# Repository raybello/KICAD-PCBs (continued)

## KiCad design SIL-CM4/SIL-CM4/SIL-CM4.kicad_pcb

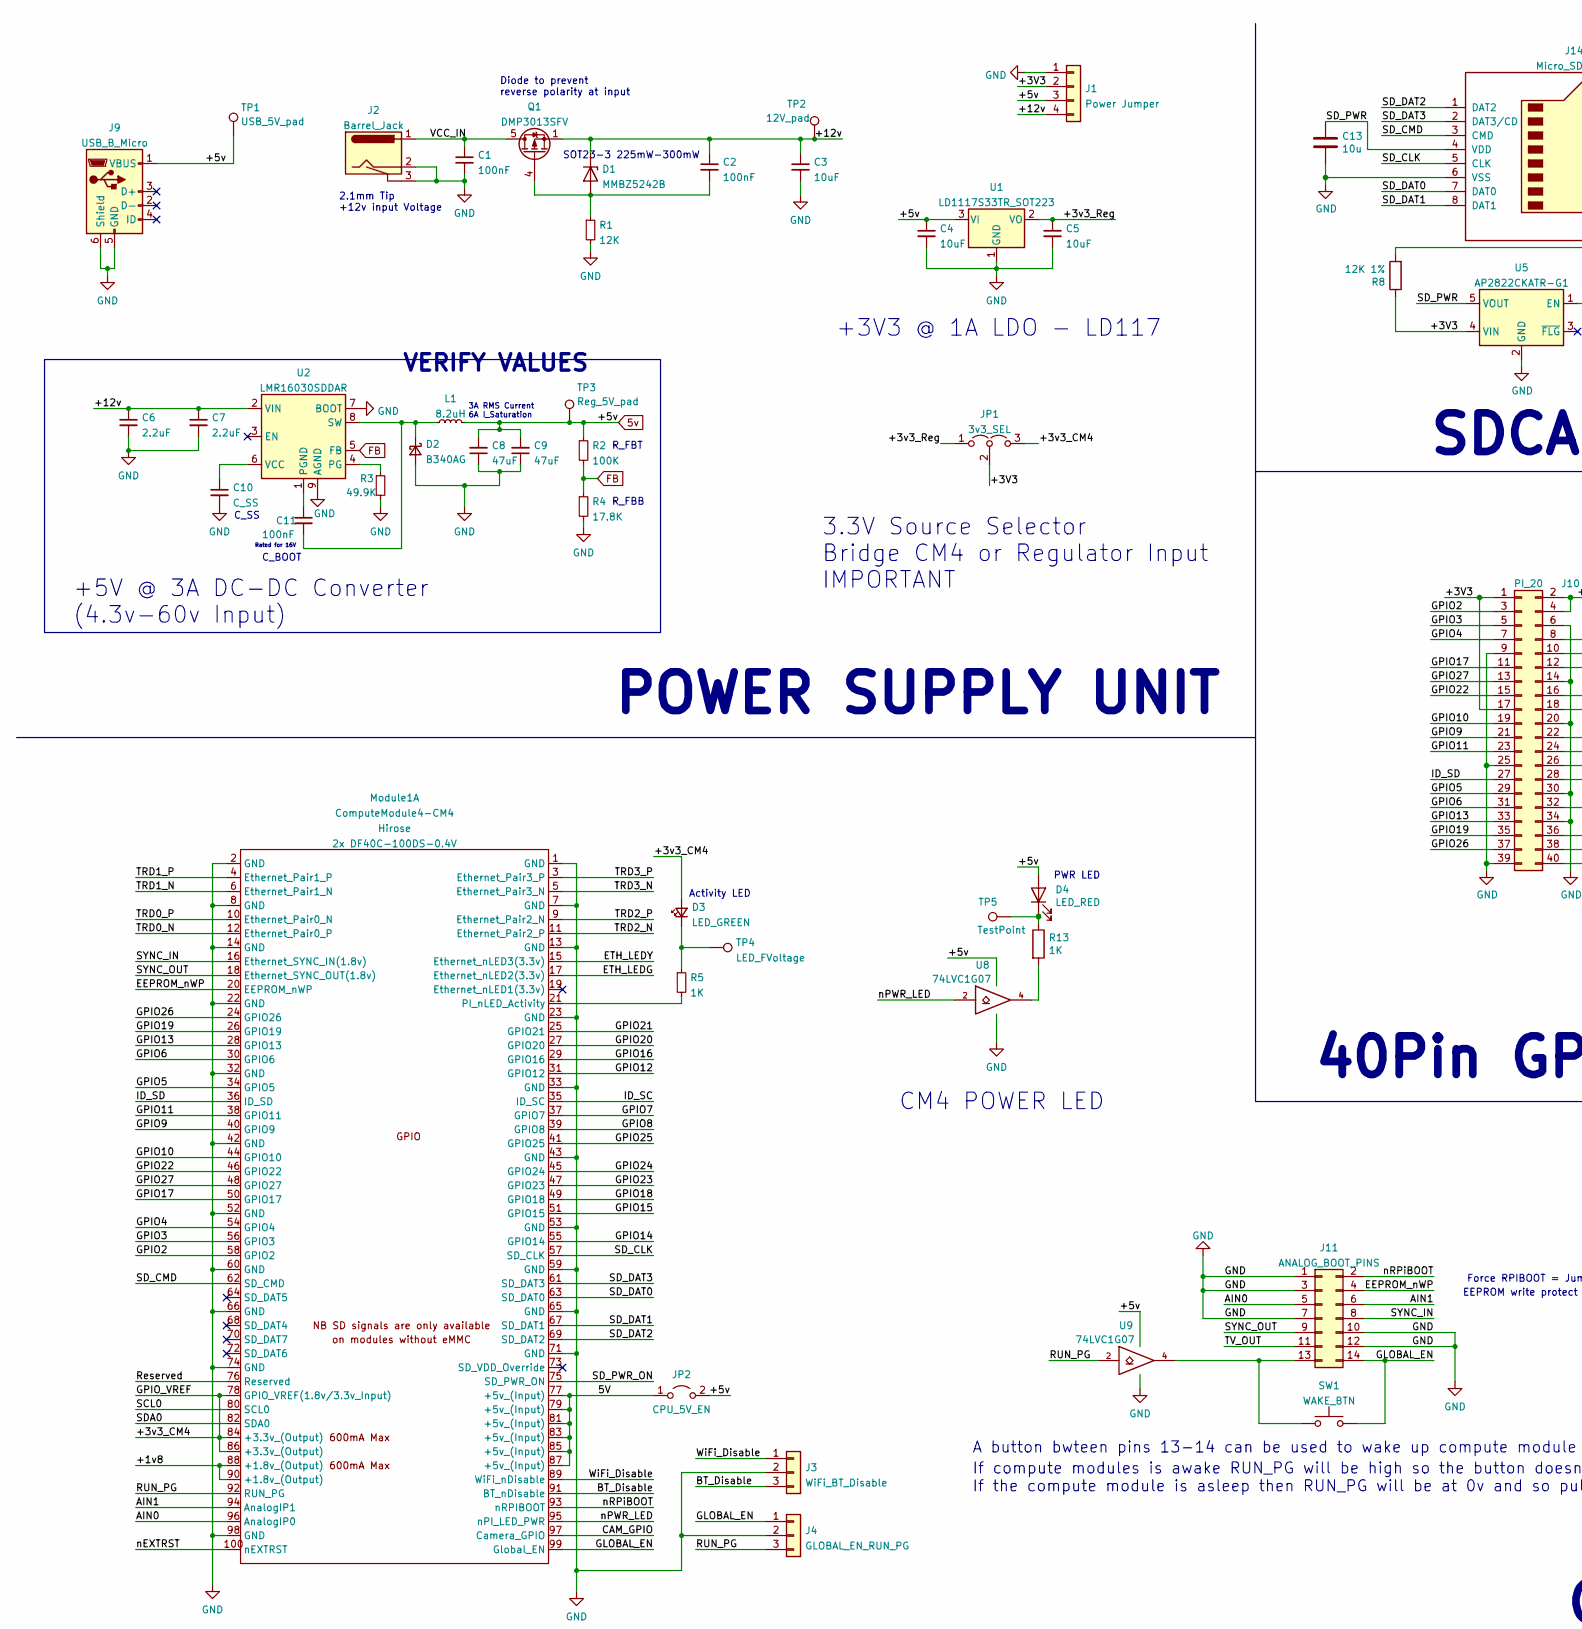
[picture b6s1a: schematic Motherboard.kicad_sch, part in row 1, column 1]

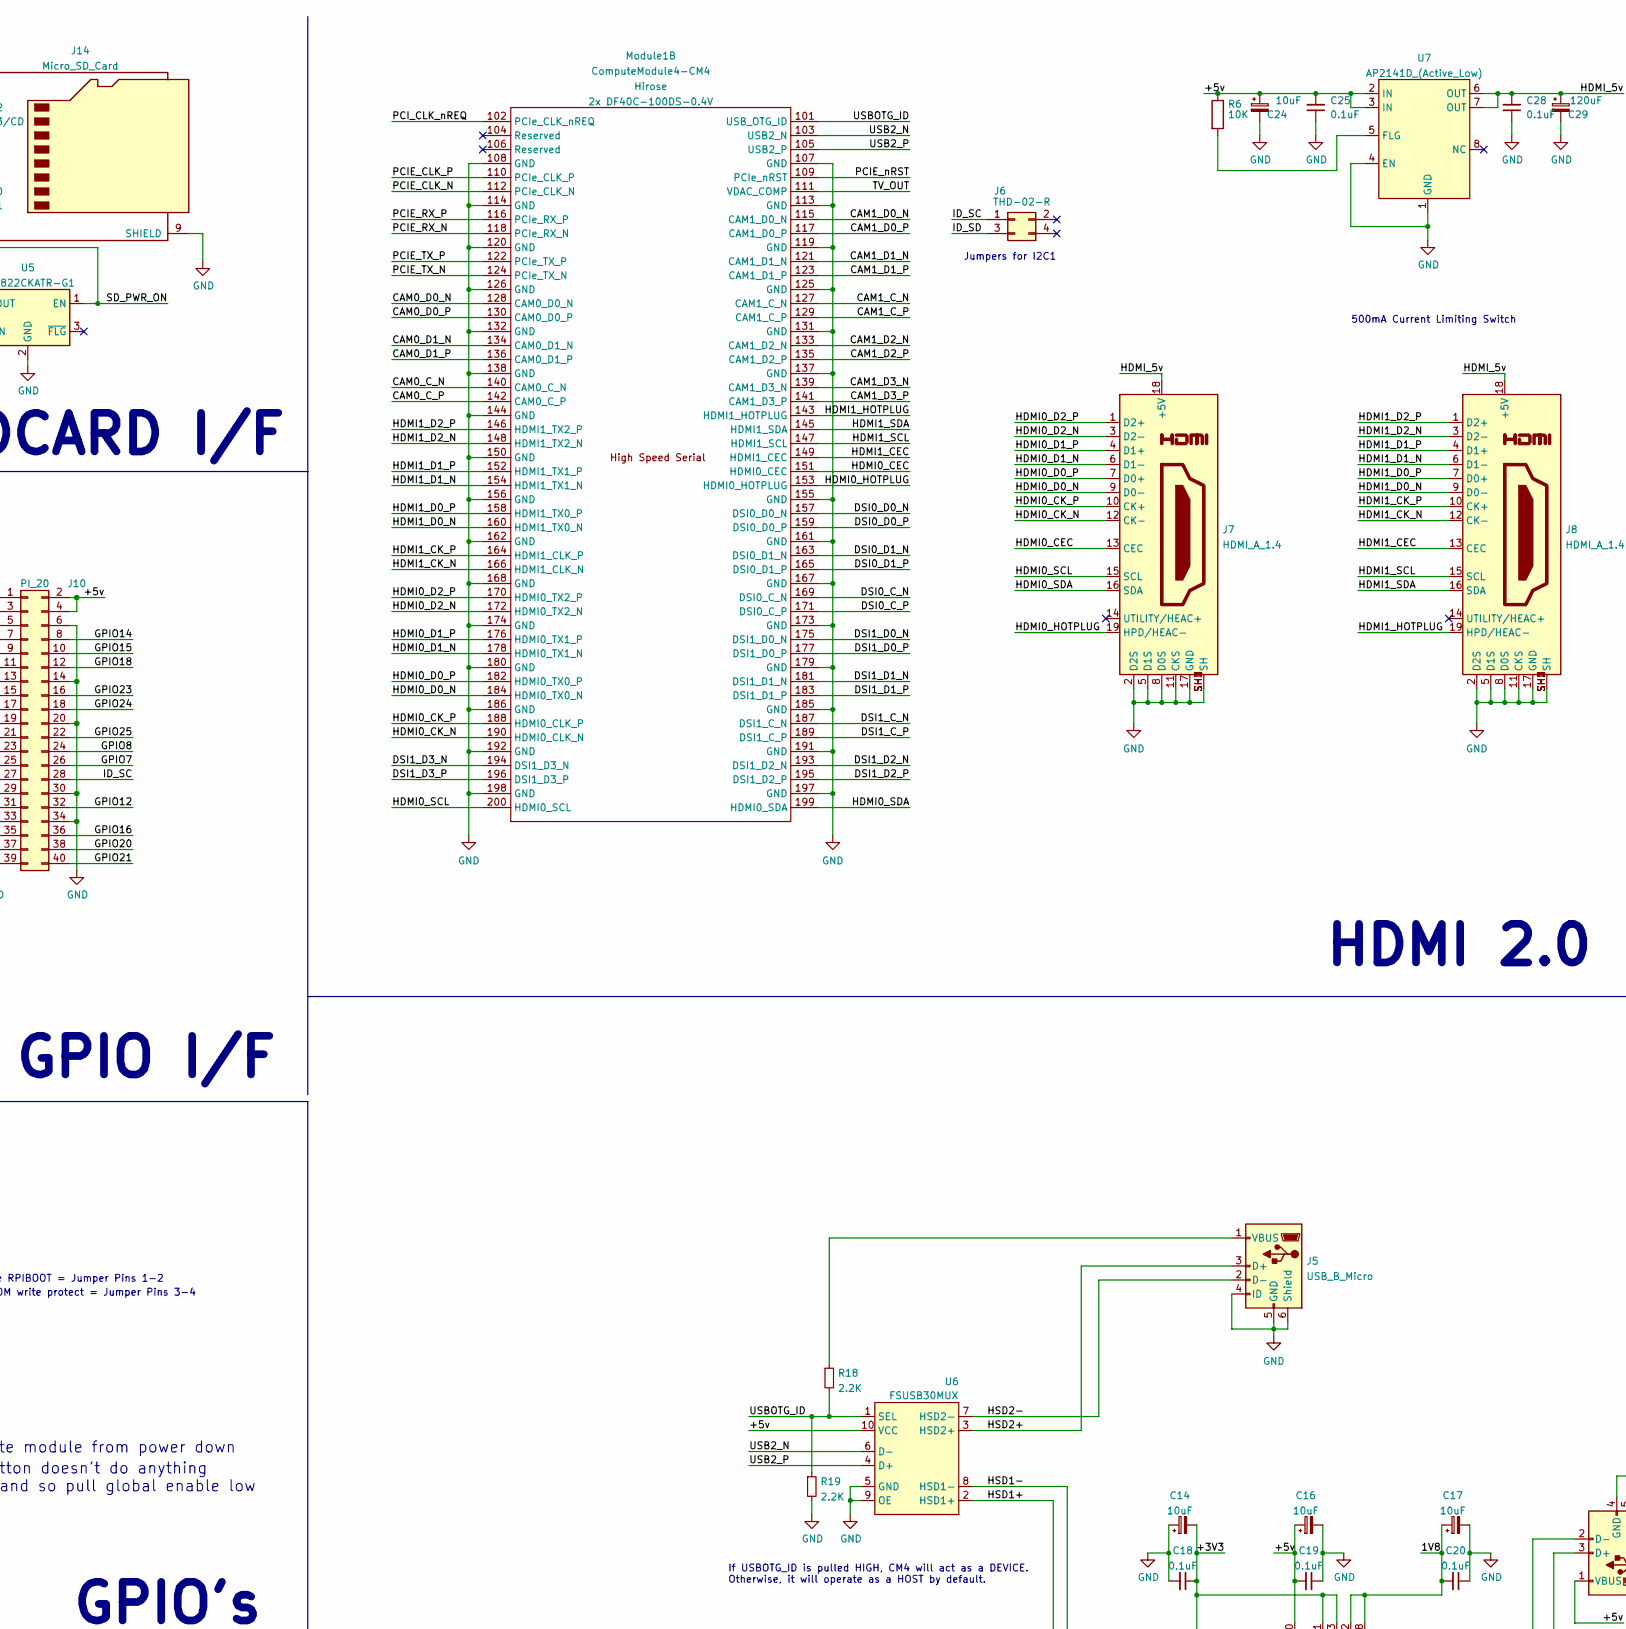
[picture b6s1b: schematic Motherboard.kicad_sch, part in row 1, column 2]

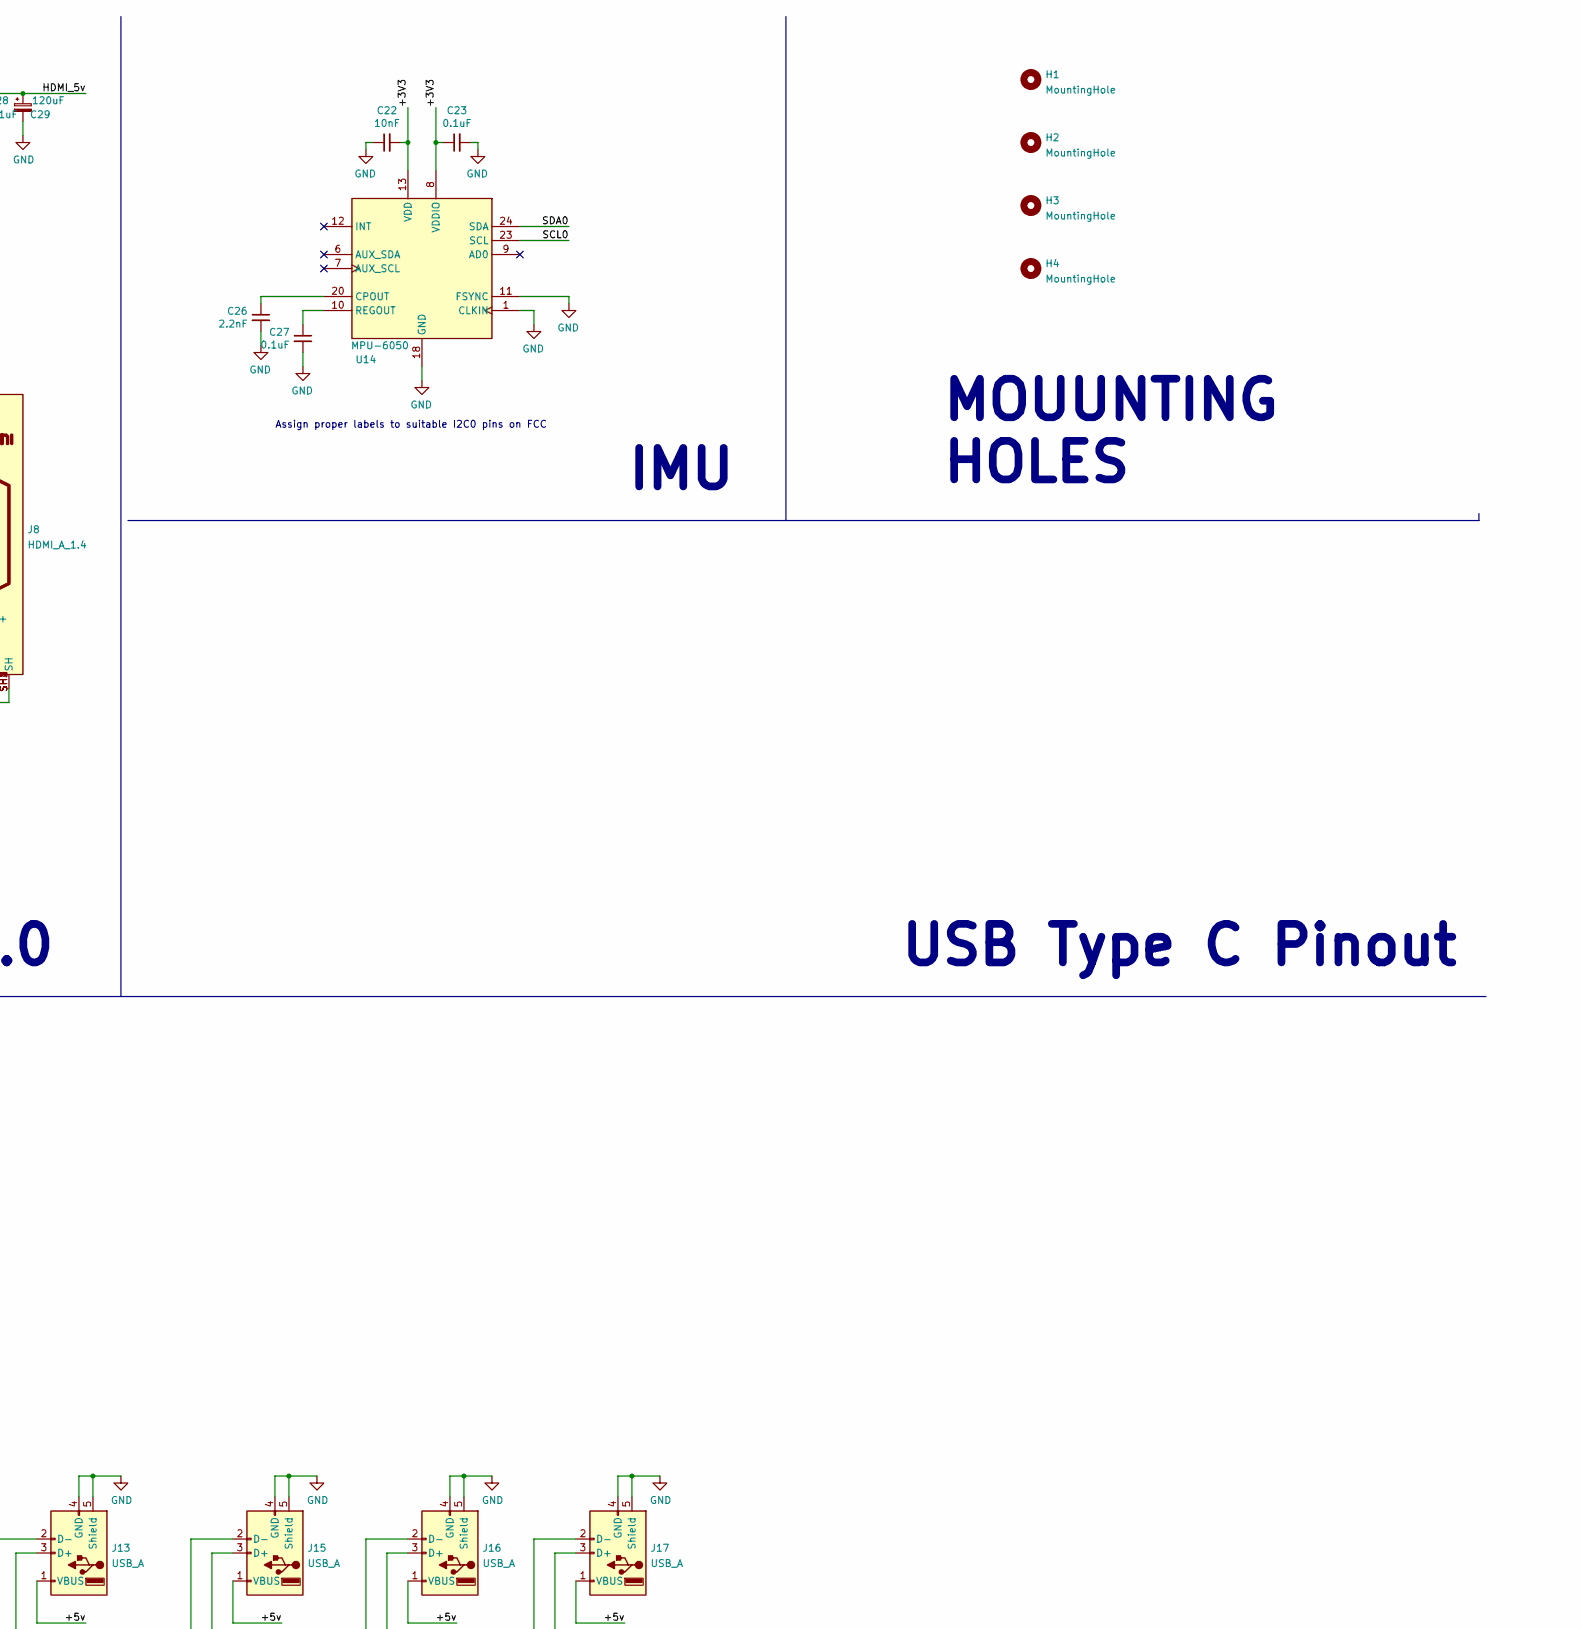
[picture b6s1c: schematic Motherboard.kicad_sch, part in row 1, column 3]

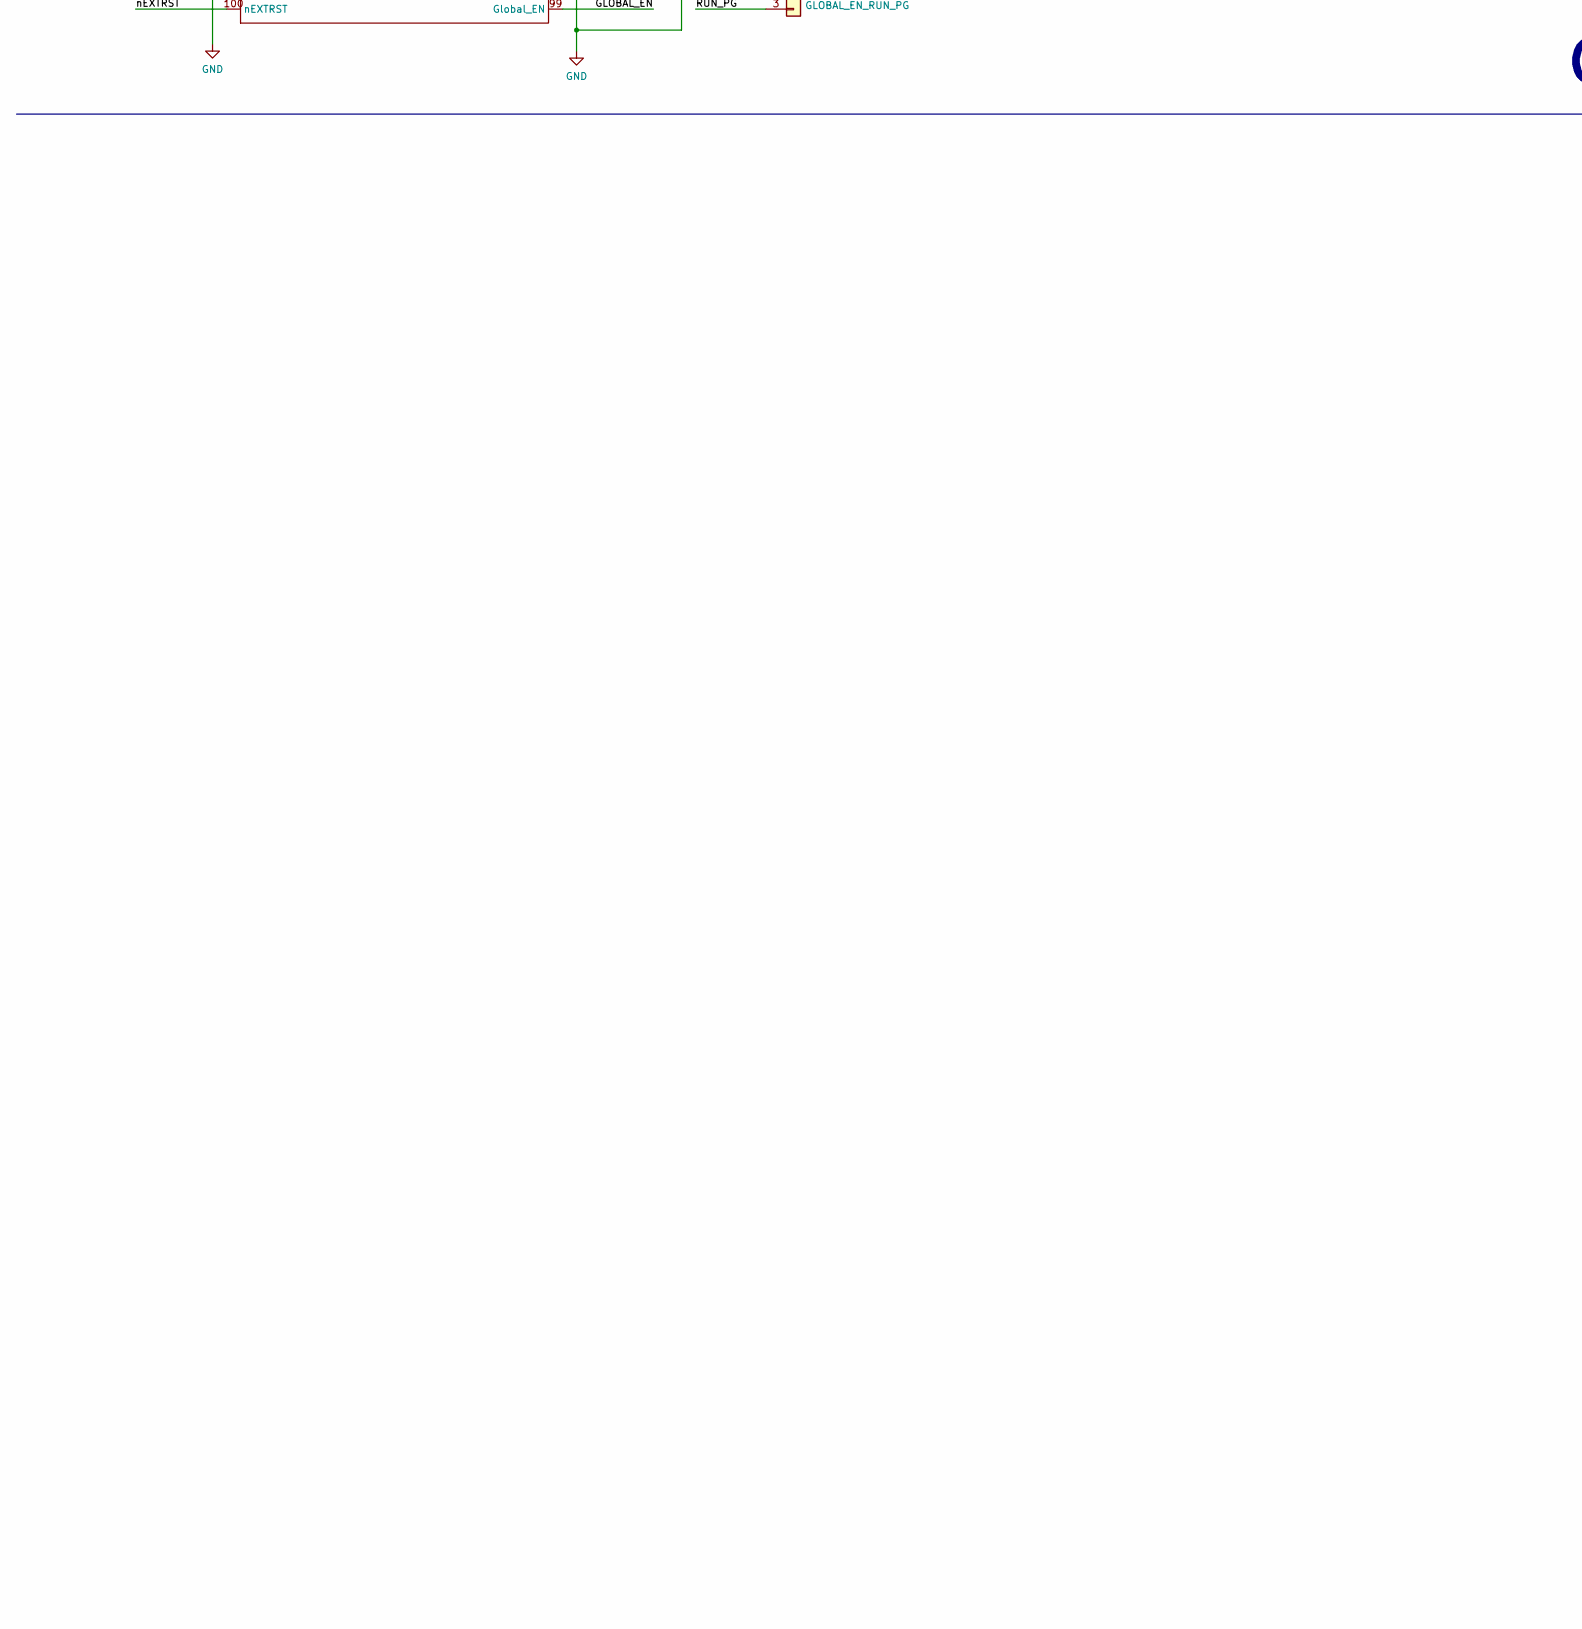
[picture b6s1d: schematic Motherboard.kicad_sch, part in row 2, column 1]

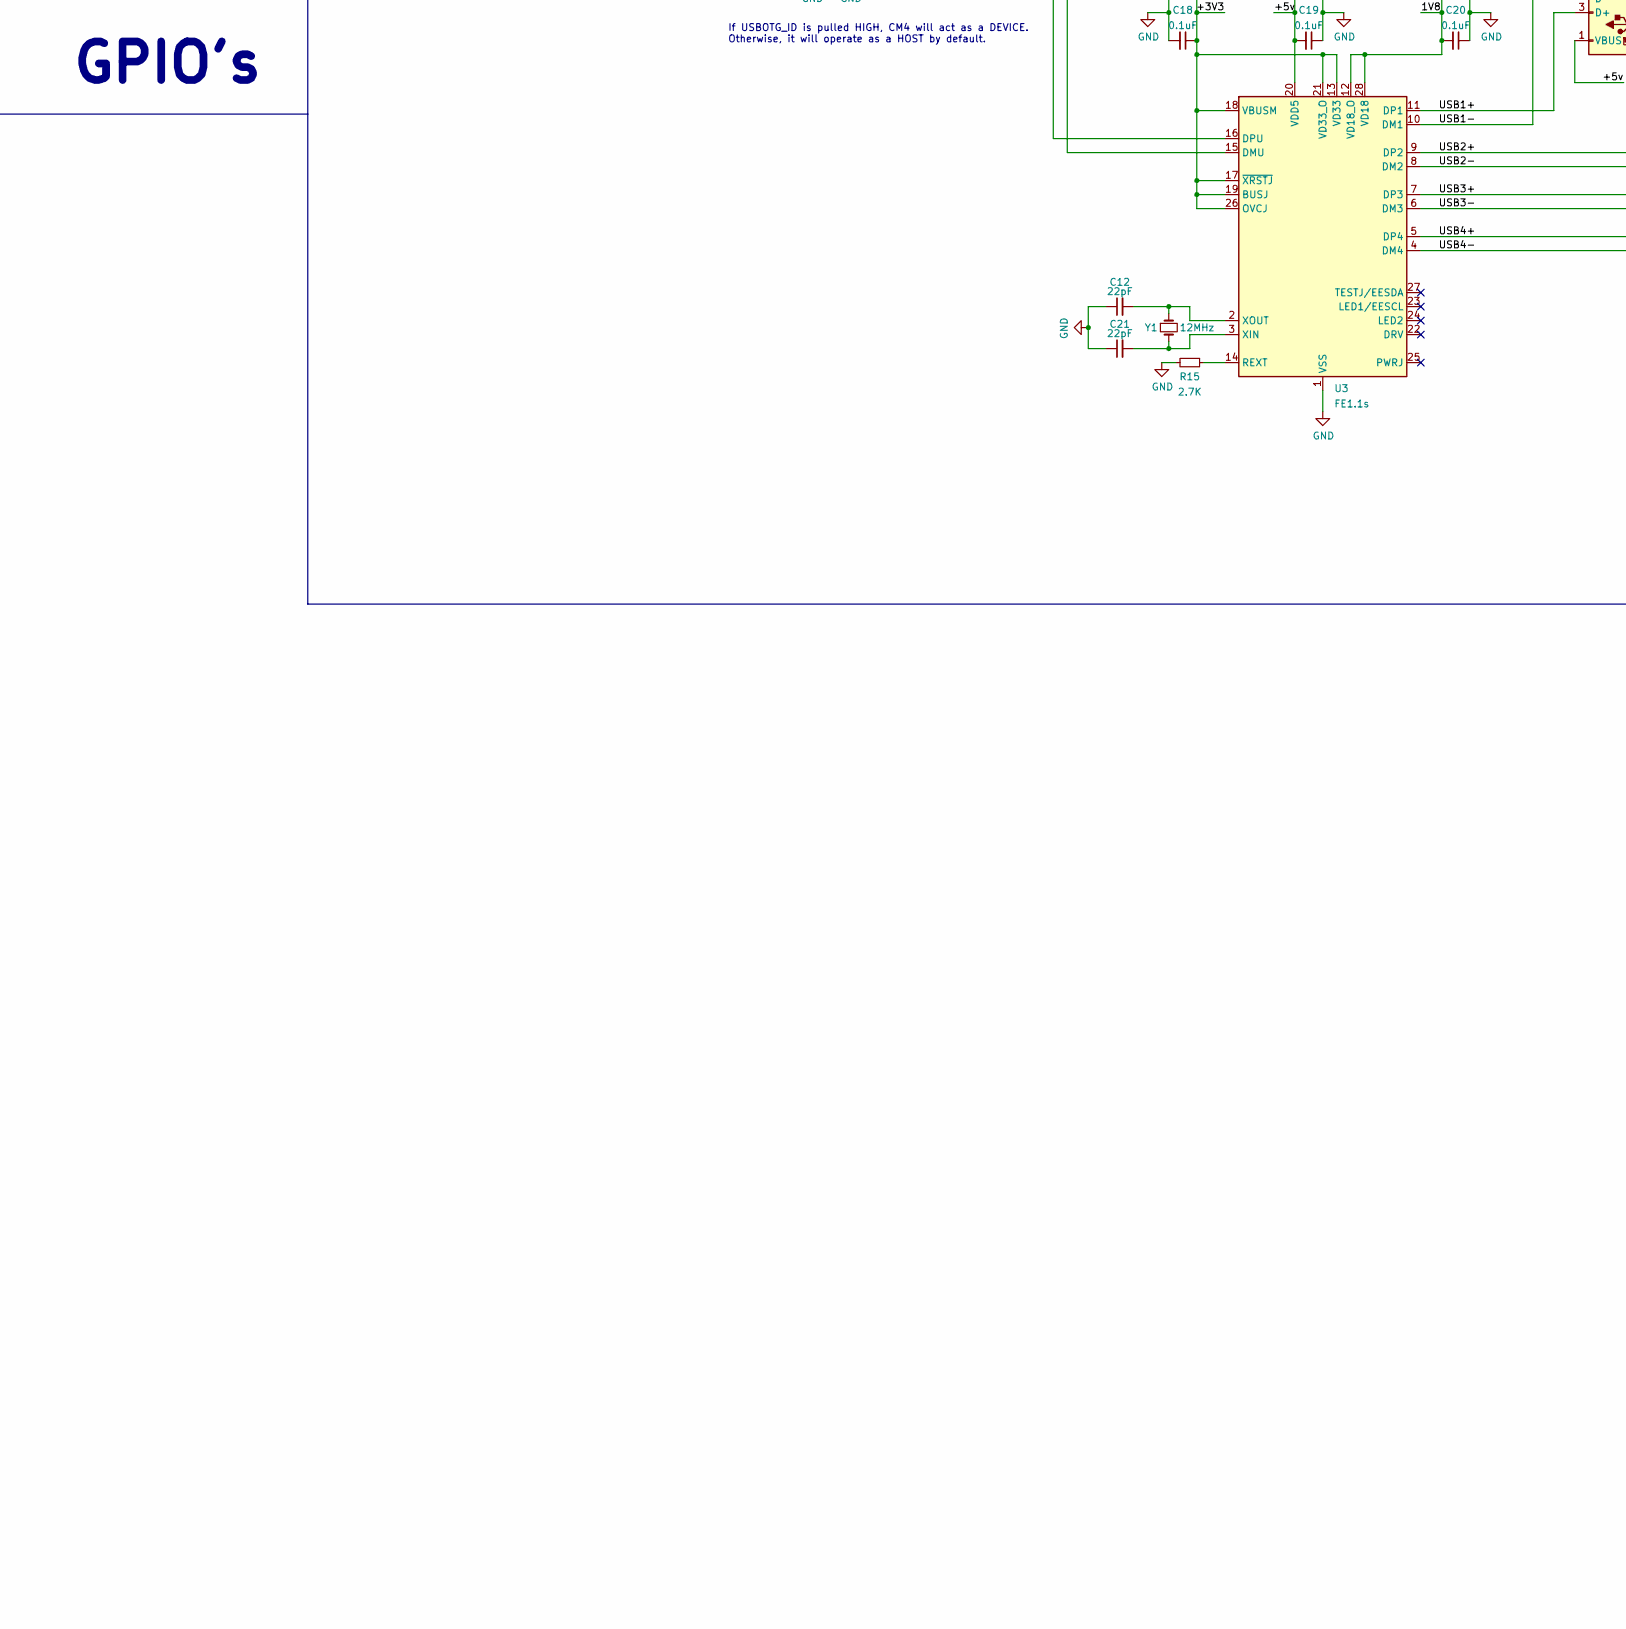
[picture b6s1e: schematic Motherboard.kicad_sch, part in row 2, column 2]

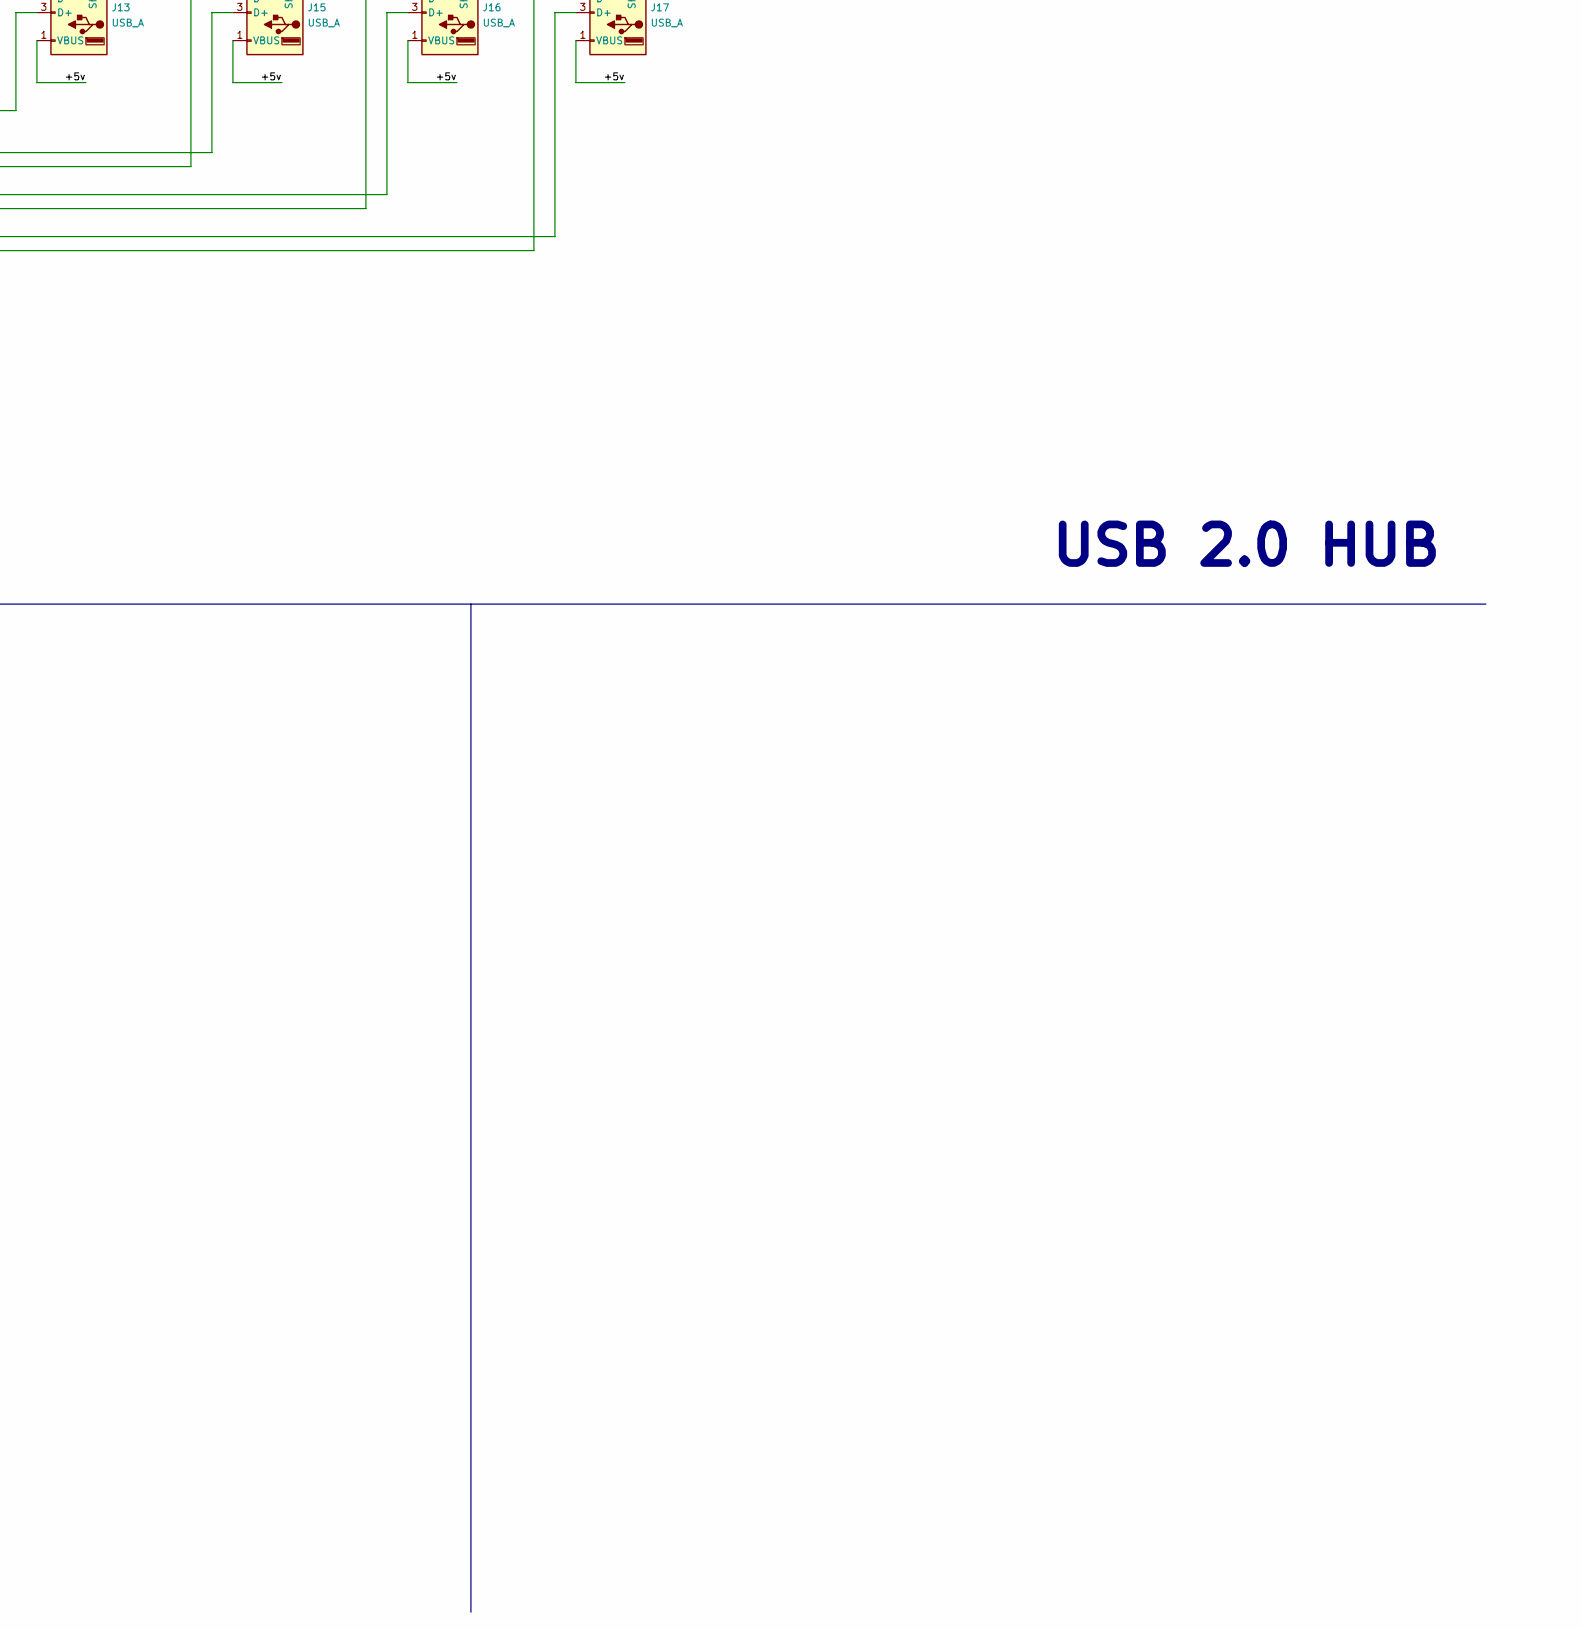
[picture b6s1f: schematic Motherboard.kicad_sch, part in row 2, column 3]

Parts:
C1, C2, C11: 100nF; C_0402_1005Metric
C3, C4, C5, C14, C16, C17, C24: 10uF; C_0402_1005Metric
C6, C7: 2.2uF; C_0402_1005Metric
C8, C9: 47uF; C_0402_1005Metric
C10: C_SS; C_0402_1005Metric
C12, C21: 22pF; C_0402_1005Metric
C13: 10u; C_0402_1005Metric; Part Description 10uF 10% 10V Ceramic Capacitor X7R 0805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
C18, C19, C20, C25, C28: 0.1uF; C_0402_1005Metric
C22: 10nF; C_0402_1005Metric_Pad0.74x0.62mm_HandSolder
C23, C27: 0.1uF; C_0402_1005Metric_Pad0.74x0.62mm_HandSolder
C26: 2.2nF; C_0402_1005Metric_Pad0.74x0.62mm_HandSolder
C29: 120uF; C_0402_1005Metric
D1: MMBZ5242B; D_SOT-23_ANK; LCSC C193729
D2: B340AG; D_SMC; LCSC C433997
D3: LED_GREEN; LED_0402_1005Metric
D4: LED_RED; LED_0402_1005Metric; Part Description Red 620nm LED Indication - Discrete 2.2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
H1, H2, H3, H4: MountingHole; MountingHole_3mm_Pad_Via
J1: Power Jumper; PinHeader_1x04_P2.54mm_Vertical
J2: Barrel_Jack; BarrelJack_CUI_PJ-063AH_Horizontal_CircularHoles; LCSC C381112
J3: WiFi_BT_Disable; PinHeader_1x03_P2.54mm_Vertical
J4: GLOBAL_EN_RUN_PG; PinHeader_1x03_P2.54mm_Vertical
J5, J9: USB_B_Micro; USB_Micro-B_Amphenol_10118194_Horizontal; LCSC C132563
J6: THD-02-R; PinHeader_2x02_P2.54mm_Vertical; Part Description PinHeader_2x02_P2.54mm_Vertical
J7, J8: HDMI_A_1.4; EDAC 690-019-298-412; LCSC C138388
J10: PI_20; PinHeader_2x20_P2.54mm_Vertical; Part Description PinHeader_2x20_P2.54mm_Vertical
J11: ANALOG_BOOT_PINS; PinHeader_2x07_P2.54mm_Vertical
J13, J15, J16, J17: USB_A; USB_A_Molex_67643_Horizontal
J14: Micro_SD_Card; microSD_HC_Wuerth_693072010801
JP1: 3v3_SEL; SolderJumper-3_P1.3mm_Open_RoundedPad1.0x1.5mm
JP2: CPU_5V_EN; SolderJumper-2_P1.3mm_Open_RoundedPad1.0x1.5mm
L1: 8.2uH; L_Bourns_SRP7028A_7.3x6.6mm; LCSC Mouser 652-SRP7028AA-8R2M
Module1: ComputeModule4-CM4; Raspberry-Pi-4-Compute-Module
Q1: DMP3013SFV; Diodes_PowerDI3333-8
R1: 12K; R_0402_1005Metric
R2: 100K; R_0402_1005Metric
R3: 49.9K; R_0402_1005Metric
R4: 17.8K; R_0402_1005Metric
R5: 1K; R_0402_1005Metric
R6: 10K; R_0402_1005Metric; Part Description Resistor 2.2K M1005 1% 63mW
R8: 12K 1%; R_0402_1005Metric; Part Description Resistor 12K M1005 1% 63mW
R13: 1K; R_0402_1005Metric; Part Description Resistor 1K M1005 1% 63mW
R15: 2.7K; R_0402_1005Metric
R18, R19: 2.2K; R_0402_1005Metric
SW1: WAKE_BTN; SW_SPST_PTS810
TP1: USB_5V_pad; TestPoint_Pad_D2.5mm
TP2: 12V_pad; TestPoint_Pad_D2.5mm
TP3: Reg_5V_pad; TestPoint_Pad_D2.5mm
TP4: LED_FVoltage; TestPoint_Pad_D2.5mm
TP5: TestPoint; TestPoint_Pad_D2.5mm
U1: LD1117S33TR_SOT223; SOT-223-3_TabPin2; LCSC C347229
U2: LMR16030SDDAR; Texas_HSOP-8-1EP_3.9x4.9mm_P1.27mm_ThermalVias; LCSC C136648
U3: FE1.1s; SSOP-28_3.9x9.9mm_P0.635mm
U5: AP2822CKATR-G1; SOT-23-5
U6: FSUSB30MUX; SOP50P490X110-10N; LCSC 512-FSUSB30MUX
U7: AP2141D_(Active_Low); MSOP-8-1EP_3x3mm_P0.65mm_EP1.68x1.88mm
U8, U9: 74LVC1G07; SOT-23-5; LCSC Mouser 595-74LVC1G07DBVTE4
U14: MPU-6050; InvenSense_QFN-24_4x4mm_P0.5mm
Y1: 12MHz; Crystal_SMD_TXC_7A-2Pin_5x3.2mm; LCSC C557138

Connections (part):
5v: C4.1, C8.2, C9.2, C16.1, C19.2, C24.1, C25.2, D4.2 (A), J1.3, J9.1 (VBUS), J10.2, J10.4, J13.1 (VBUS), J15.1 (VBUS), J16.1 (VBUS), J17.1 (VBUS), JP2.2 (B), L1.2, R2.1, R6.1, TP1.1, TP3.1, U1.3 (VI), U3.20 (VDD5), U6.10 (VCC), U7.2 (IN), U7.3 (IN), U8.5 (VCC), U9.5 (VCC)
/SIL-Motherboard/1V8: C17.1, C20.2, U3.12 (VD18_O), U3.28 (VD18)
/SIL-Motherboard/5V: JP2.1 (A), Module1.77 (+5v_(Input)), Module1.79 (+5v_(Input)), Module1.81 (+5v_(Input)), Module1.83 (+5v_(Input)), Module1.85 (+5v_(Input)), Module1.87 (+5v_(Input))
/SIL-Motherboard/+1v8: Module1.88 (+1.8v_(Output)), Module1.90 (+1.8v_(Output))
/SIL-Motherboard/+3V3: C14.2, C18.1, C22.2, C23.1, J1.2, J10.1, J10.17, JP1.2 (C), R8.1, U3.13 (VD33), U3.17 (~XRSTJ), U3.18 (VBUSM), U3.19 (BUSJ), U3.21 (VD33_O), U3.26 (OVCJ), U5.4 (VIN), U14.8 (VDDIO), U14.13 (VDD)
/SIL-Motherboard/+3v3_CM4: D3.2 (A), JP1.3 (B), Module1.78 (GPIO_VREF(1.8v/3.3v_Input)), Module1.84 (+3.3v_(Output)), Module1.86 (+3.3v_(Output))
/SIL-Motherboard/+3v3_Reg: C5.1, JP1.1 (A), U1.2 (VO)
/SIL-Motherboard/+12v: C2.1, C3.1, C6.1, C7.1, D1.1 (K), J1.4, Q1.1 (S), Q1.2 (S), Q1.3 (S), TP2.1, U2.2 (VIN)
/SIL-Motherboard/AIN0: J11.5, Module1.96 (AnalogIP0)
/SIL-Motherboard/AIN1: J11.6, Module1.94 (AnalogIP1)
/SIL-Motherboard/BT_Disable: J3.3, Module1.91 (BT_nDisable)
/SIL-Motherboard/CAM0_C_N: Module1.140 (CAM0_C_N)
/SIL-Motherboard/CAM0_C_P: Module1.142 (CAM0_C_P)
/SIL-Motherboard/CAM0_D0_N: Module1.128 (CAM0_D0_N)
/SIL-Motherboard/CAM0_D0_P: Module1.130 (CAM0_D0_P)
/SIL-Motherboard/CAM0_D1_N: Module1.134 (CAM0_D1_N)
/SIL-Motherboard/CAM0_D1_P: Module1.136 (CAM0_D1_P)
/SIL-Motherboard/CAM1_C_N: Module1.127 (CAM1_C_N)
/SIL-Motherboard/CAM1_C_P: Module1.129 (CAM1_C_P)
/SIL-Motherboard/CAM1_D0_N: Module1.115 (CAM1_D0_N)
/SIL-Motherboard/CAM1_D0_P: Module1.117 (CAM1_D0_P)
/SIL-Motherboard/CAM1_D1_N: Module1.121 (CAM1_D1_N)
/SIL-Motherboard/CAM1_D1_P: Module1.123 (CAM1_D1_P)
/SIL-Motherboard/CAM1_D2_N: Module1.133 (CAM1_D2_N)
/SIL-Motherboard/CAM1_D2_P: Module1.135 (CAM1_D2_P)
/SIL-Motherboard/CAM1_D3_N: Module1.139 (CAM1_D3_N)
/SIL-Motherboard/CAM1_D3_P: Module1.141 (CAM1_D3_P)
/SIL-Motherboard/CAM_GPIO: Module1.97 (Camera_GPIO)
/SIL-Motherboard/DSI0_C_N: Module1.169 (DSI0_C_N)
/SIL-Motherboard/DSI0_C_P: Module1.171 (DSI0_C_P)
/SIL-Motherboard/DSI0_D0_N: Module1.157 (DSI0_D0_N)
/SIL-Motherboard/DSI0_D0_P: Module1.159 (DSI0_D0_P)
/SIL-Motherboard/DSI0_D1_N: Module1.163 (DSI0_D1_N)
/SIL-Motherboard/DSI0_D1_P: Module1.165 (DSI0_D1_P)
/SIL-Motherboard/DSI1_C_N: Module1.187 (DSI1_C_N)
/SIL-Motherboard/DSI1_C_P: Module1.189 (DSI1_C_P)
/SIL-Motherboard/DSI1_D0_N: Module1.175 (DSI1_D0_N)
/SIL-Motherboard/DSI1_D0_P: Module1.177 (DSI1_D0_P)
/SIL-Motherboard/DSI1_D1_N: Module1.181 (DSI1_D1_N)
/SIL-Motherboard/DSI1_D1_P: Module1.183 (DSI1_D1_P)
/SIL-Motherboard/DSI1_D2_N: Module1.193 (DSI1_D2_N)
/SIL-Motherboard/DSI1_D2_P: Module1.195 (DSI1_D2_P)
/SIL-Motherboard/DSI1_D3_N: Module1.194 (DSI1_D3_N)
/SIL-Motherboard/DSI1_D3_P: Module1.196 (DSI1_D3_P)
/SIL-Motherboard/EEPROM_nWP: J11.4, Module1.20 (EEPROM_nWP)
/SIL-Motherboard/ETH_LEDG: Module1.17 (Ethernet_nLED2(3.3v))
/SIL-Motherboard/ETH_LEDY: Module1.15 (Ethernet_nLED3(3.3v))
/SIL-Motherboard/GLOBAL_EN: J4.1, J11.14, Module1.99 (Global_EN), SW1.2
/SIL-Motherboard/GPIO2: J10.3, Module1.58 (GPIO2)
/SIL-Motherboard/GPIO3: J10.5, Module1.56 (GPIO3)
/SIL-Motherboard/GPIO4: J10.7, Module1.54 (GPIO4)
/SIL-Motherboard/GPIO5: J10.29, Module1.34 (GPIO5)
/SIL-Motherboard/GPIO6: J10.31, Module1.30 (GPIO6)
/SIL-Motherboard/GPIO7: J10.26, Module1.37 (GPIO7)
/SIL-Motherboard/GPIO8: J10.24, Module1.39 (GPIO8)
/SIL-Motherboard/GPIO9: J10.21, Module1.40 (GPIO9)
/SIL-Motherboard/GPIO10: J10.19, Module1.44 (GPIO10)
/SIL-Motherboard/GPIO11: J10.23, Module1.38 (GPIO11)
/SIL-Motherboard/GPIO12: J10.32, Module1.31 (GPIO12)
/SIL-Motherboard/GPIO13: J10.33, Module1.28 (GPIO13)
/SIL-Motherboard/GPIO14: J10.8, Module1.55 (GPIO14)
/SIL-Motherboard/GPIO15: J10.10, Module1.51 (GPIO15)
/SIL-Motherboard/GPIO16: J10.36, Module1.29 (GPIO16)
/SIL-Motherboard/GPIO17: J10.11, Module1.50 (GPIO17)
/SIL-Motherboard/GPIO18: J10.12, Module1.49 (GPIO18)
/SIL-Motherboard/GPIO19: J10.35, Module1.26 (GPIO19)
/SIL-Motherboard/GPIO20: J10.38, Module1.27 (GPIO20)
/SIL-Motherboard/GPIO21: J10.40, Module1.25 (GPIO21)
/SIL-Motherboard/GPIO22: J10.15, Module1.46 (GPIO22)
/SIL-Motherboard/GPIO23: J10.16, Module1.47 (GPIO23)
/SIL-Motherboard/GPIO24: J10.18, Module1.45 (GPIO24)
/SIL-Motherboard/GPIO25: J10.22, Module1.41 (GPIO25)
/SIL-Motherboard/GPIO26: J10.37, Module1.24 (GPIO26)
/SIL-Motherboard/GPIO27: J10.13, Module1.48 (GPIO27)
/SIL-Motherboard/HDMI0_CEC: J7.13 (CEC), Module1.151 (HDMI0_CEC)
/SIL-Motherboard/HDMI0_CK_N: J7.12 (CK-), Module1.190 (HDMI0_CLK_N)
/SIL-Motherboard/HDMI0_CK_P: J7.10 (CK+), Module1.188 (HDMI0_CLK_P)
/SIL-Motherboard/HDMI0_D0_N: J7.9 (D0-), Module1.184 (HDMI0_TX0_N)
/SIL-Motherboard/HDMI0_D0_P: J7.7 (D0+), Module1.182 (HDMI0_TX0_P)
/SIL-Motherboard/HDMI0_D1_N: J7.6 (D1-), Module1.178 (HDMI0_TX1_N)
/SIL-Motherboard/HDMI0_D1_P: J7.4 (D1+), Module1.176 (HDMI0_TX1_P)
/SIL-Motherboard/HDMI0_D2_N: J7.3 (D2-), Module1.172 (HDMI0_TX2_N)
/SIL-Motherboard/HDMI0_D2_P: J7.1 (D2+), Module1.170 (HDMI0_TX2_P)
/SIL-Motherboard/HDMI0_HOTPLUG: J7.19 (HPD/HEAC-), Module1.153 (HDMI0_HOTPLUG)
/SIL-Motherboard/HDMI0_SCL: J7.15 (SCL), Module1.200 (HDMI0_SCL)
/SIL-Motherboard/HDMI0_SDA: J7.16 (SDA), Module1.199 (HDMI0_SDA)
/SIL-Motherboard/HDMI1_CEC: J8.13 (CEC), Module1.149 (HDMI1_CEC)
/SIL-Motherboard/HDMI1_CK_N: J8.12 (CK-), Module1.166 (HDMI1_CLK_N)
/SIL-Motherboard/HDMI1_CK_P: J8.10 (CK+), Module1.164 (HDMI1_CLK_P)
/SIL-Motherboard/HDMI1_D0_N: J8.9 (D0-), Module1.160 (HDMI1_TX0_N)
/SIL-Motherboard/HDMI1_D0_P: J8.7 (D0+), Module1.158 (HDMI1_TX0_P)
/SIL-Motherboard/HDMI1_D1_N: J8.6 (D1-), Module1.154 (HDMI1_TX1_N)
/SIL-Motherboard/HDMI1_D1_P: J8.4 (D1+), Module1.152 (HDMI1_TX1_P)
/SIL-Motherboard/HDMI1_D2_N: J8.3 (D2-), Module1.148 (HDMI1_TX2_N)
/SIL-Motherboard/HDMI1_D2_P: J8.1 (D2+), Module1.146 (HDMI1_TX2_P)
/SIL-Motherboard/HDMI1_HOTPLUG: J8.19 (HPD/HEAC-), Module1.143 (HDMI1_HOTPLUG)
/SIL-Motherboard/HDMI1_SCL: J8.15 (SCL), Module1.147 (HDMI1_SCL)
/SIL-Motherboard/HDMI1_SDA: J8.16 (SDA), Module1.145 (HDMI1_SDA)
/SIL-Motherboard/HDMI_5v: C28.2, C29.1, J7.18 (+5V), J8.18 (+5V), U7.6 (OUT), U7.7 (OUT)
/SIL-Motherboard/HSD1+: U3.16 (DPU), U6.2 (HSD1+)
/SIL-Motherboard/HSD1-: U3.15 (DMU), U6.8 (HSD1-)
/SIL-Motherboard/HSD2+: J5.3 (D+), U6.3 (HSD2+)
/SIL-Motherboard/HSD2-: J5.2 (D-), U6.7 (HSD2-)
/SIL-Motherboard/ID_SC: J6.1, J10.28, Module1.35 (ID_SC)
/SIL-Motherboard/ID_SD: J6.3, J10.27, Module1.36 (ID_SD)
/SIL-Motherboard/PCIE_CLK_N: Module1.112 (PCIe_CLK_N)
/SIL-Motherboard/PCIE_CLK_P: Module1.110 (PCIe_CLK_P)
/SIL-Motherboard/PCIE_RX_N: Module1.118 (PCIe_RX_N)
/SIL-Motherboard/PCIE_RX_P: Module1.116 (PCIe_RX_P)
/SIL-Motherboard/PCIE_TX_N: Module1.124 (PCIe_TX_N)
/SIL-Motherboard/PCIE_TX_P: Module1.122 (PCIe_TX_P)
/SIL-Motherboard/PCIE_nRST: Module1.109 (PCIe_nRST)
/SIL-Motherboard/PCI_CLK_nREQ: Module1.102 (PCIe_CLK_nREQ)
/SIL-Motherboard/RUN_PG: J4.3, Module1.92 (RUN_PG), U9.2
/SIL-Motherboard/Reserved: Module1.76 (Reserved)
/SIL-Motherboard/SCL0: Module1.80 (SCL0), U14.23 (SCL)
/SIL-Motherboard/SDA0: Module1.82 (SDA0), U14.24 (SDA)
/SIL-Motherboard/SD_CLK: J14.5 (CLK), Module1.57 (SD_CLK)
/SIL-Motherboard/SD_CMD: J14.3 (CMD), Module1.62 (SD_CMD)
/SIL-Motherboard/SD_DAT0: J14.7 (DAT0), Module1.63 (SD_DAT0)
/SIL-Motherboard/SD_DAT1: J14.8 (DAT1), Module1.67 (SD_DAT1)
/SIL-Motherboard/SD_DAT2: J14.1 (DAT2), Module1.69 (SD_DAT2)
/SIL-Motherboard/SD_DAT3: J14.2 (DAT3/CD), Module1.61 (SD_DAT3)
/SIL-Motherboard/SD_PWR: C13.1, J14.4 (VDD), U5.5 (VOUT)
/SIL-Motherboard/SD_PWR_ON: Module1.75 (SD_PWR_ON), R8.2, U5.1 (EN)
/SIL-Motherboard/SYNC_IN: J11.8, Module1.16 (Ethernet_SYNC_IN(1.8v))
/SIL-Motherboard/SYNC_OUT: J11.9, Module1.18 (Ethernet_SYNC_OUT(1.8v))
/SIL-Motherboard/TRD0_N: Module1.12 (Ethernet_Pair0_P)
/SIL-Motherboard/TRD0_P: Module1.10 (Ethernet_Pair0_N)
/SIL-Motherboard/TRD1_N: Module1.6 (Ethernet_Pair1_N)
/SIL-Motherboard/TRD1_P: Module1.4 (Ethernet_Pair1_P)
/SIL-Motherboard/TRD2_N: Module1.11 (Ethernet_Pair2_P)
/SIL-Motherboard/TRD2_P: Module1.9 (Ethernet_Pair2_N)
/SIL-Motherboard/TRD3_N: Module1.5 (Ethernet_Pair3_N)
/SIL-Motherboard/TRD3_P: Module1.3 (Ethernet_Pair3_P)
/SIL-Motherboard/TV_OUT: J11.11, Module1.111 (VDAC_COMP)
/SIL-Motherboard/USB1+: J13.3 (D+), U3.11 (DP1)
/SIL-Motherboard/USB1-: J13.2 (D-), U3.10 (DM1)
/SIL-Motherboard/USB2+: J15.3 (D+), U3.9 (DP2)
/SIL-Motherboard/USB2-: J15.2 (D-), U3.8 (DM2)
/SIL-Motherboard/USB2_N: Module1.103 (USB2_N), U6.6 (D-)
/SIL-Motherboard/USB2_P: Module1.105 (USB2_P), U6.4 (D+)
/SIL-Motherboard/USB3+: J16.3 (D+), U3.7 (DP3)
/SIL-Motherboard/USB3-: J16.2 (D-), U3.6 (DM3)
/SIL-Motherboard/USB4+: J17.3 (D+), U3.5 (DP4)
/SIL-Motherboard/USB4-: J17.2 (D-), U3.4 (DM4)
/SIL-Motherboard/USBOTG_ID: Module1.101 (USB_OTG_ID), R18.2, R19.1, U6.1 (SEL)
/SIL-Motherboard/VCC_IN: C1.1, J2.1, Q1.5 (D)
/SIL-Motherboard/WiFi_Disable: J3.1, Module1.89 (WiFi_nDisable)
/SIL-Motherboard/nEXTRST: Module1.100 (nEXTRST)
/SIL-Motherboard/nPWR_LED: Module1.95 (nPI_LED_PWR), U8.2
/SIL-Motherboard/nRPiBOOT: J11.2, Module1.93 (nRPIBOOT)
FB: R2.2, R4.1, U2.5 (FB)
GND: C1.2, C3.2, C4.2, C5.2, C6.2, C7.2, C8.1, C9.1, C10.2, C12.1, C13.2, C14.1, C16.2, C17.2, C18.2, C19.1, C20.1, C21.1, C22.1, C23.2, C24.2, C25.1, C26.2, C27.2, C28.1, C29.2, D2.2 (A), J1.1, J2.2, J2.3, J3.2, J4.2, J5.4 (ID), J5.5 (GND), J5.6 (Shield), J7.2 (D2S), J7.5 (D1S), J7.8 (D0S), J7.11 (CKS), J7.17 (GND), J7.SH1 (SH), J7.SH2 (SH), J7.SH3 (SH), J7.SH4 (SH), J8.2 (D2S), J8.5 (D1S), J8.8 (D0S), J8.11 (CKS), J8.17 (GND), J8.SH1 (SH), J8.SH2 (SH), J8.SH3 (SH), J8.SH4 (SH), J9.5 (GND), J9.6 (Shield), J10.6, J10.9, J10.14, J10.20, J10.25, J10.30, J10.34, J10.39, J11.1, J11.3, J11.7, J11.10, J11.12, J13.4 (GND), J13.5 (Shield), J14.6 (VSS), J14.9 (SHIELD), J15.4 (GND), J15.5 (Shield), J16.4 (GND), J16.5 (Shield), J17.4 (GND), J17.5 (Shield), Module1.1 (GND), Module1.2 (GND), Module1.7 (GND)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
unnamed: C2.2, D1.2 (A), Q1.4 (G), R1.1
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
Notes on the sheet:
Jumpers for I2C1
+3V3 @ 1A LDO - LD117
Diode to prevent reverse polarity at input
VERIFY VALUES
Activity LED
500mA Current Limiting Switch
EEPROM write protect = Jumper Pins 3-4
3.3V Source Selector Bridge CM4 or Regulator Input IMPORTANT
C_SS
A button bwteen pins 13-14 can be used to wake up compute module from power down
CM4 POWER LED
Assign proper labels to suitable I2C0 pins on FCC
USB 2.0 HUB
40Pin GPIO I/F
Force RPIBOOT = Jumper Pins 1-2
HDMI 2.0
IMU
PWR LED
If compute modules is awake RUN_PG will be high so the button doesn't do anything If the compute module is asleep then RUN_PG will be at 0v and so pull global enable low
3A RMS Current 6A I_Saturation
R_FBT
R_FBB
POWER SUPPLY UNIT
GPIO's
C_BOOT
SDCARD I/F
USB Type C Pinout
If USBOTG_ID is pulled HIGH, CM4 will act as a DEVICE. Otherwise, it will operate as a HOST by default.
+5V @ 3A DC-DC Converter (4.3v-60v Input)
MOUUNTING HOLES
SOT23-3 225mW-300mW
Rated for 16V
2.1mm Tip +12v input Voltage
